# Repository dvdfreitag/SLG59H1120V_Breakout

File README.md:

# SLG59H1120V_Breakout
A SLG59H1120V breakout board

The [SLG59H1120V](https://www.digikey.com/product-detail/en/silego-technology/SLG59H1120V/1827-1055-1-ND/7562939) is an extremely inexpensive high side power switch with a rich feature set. This chip has built in current limiting with a current set resistor, soft start, thermal cutoff, configurable input over voltage protection, short circuit protection, current output, and an open drain fault interrupt.

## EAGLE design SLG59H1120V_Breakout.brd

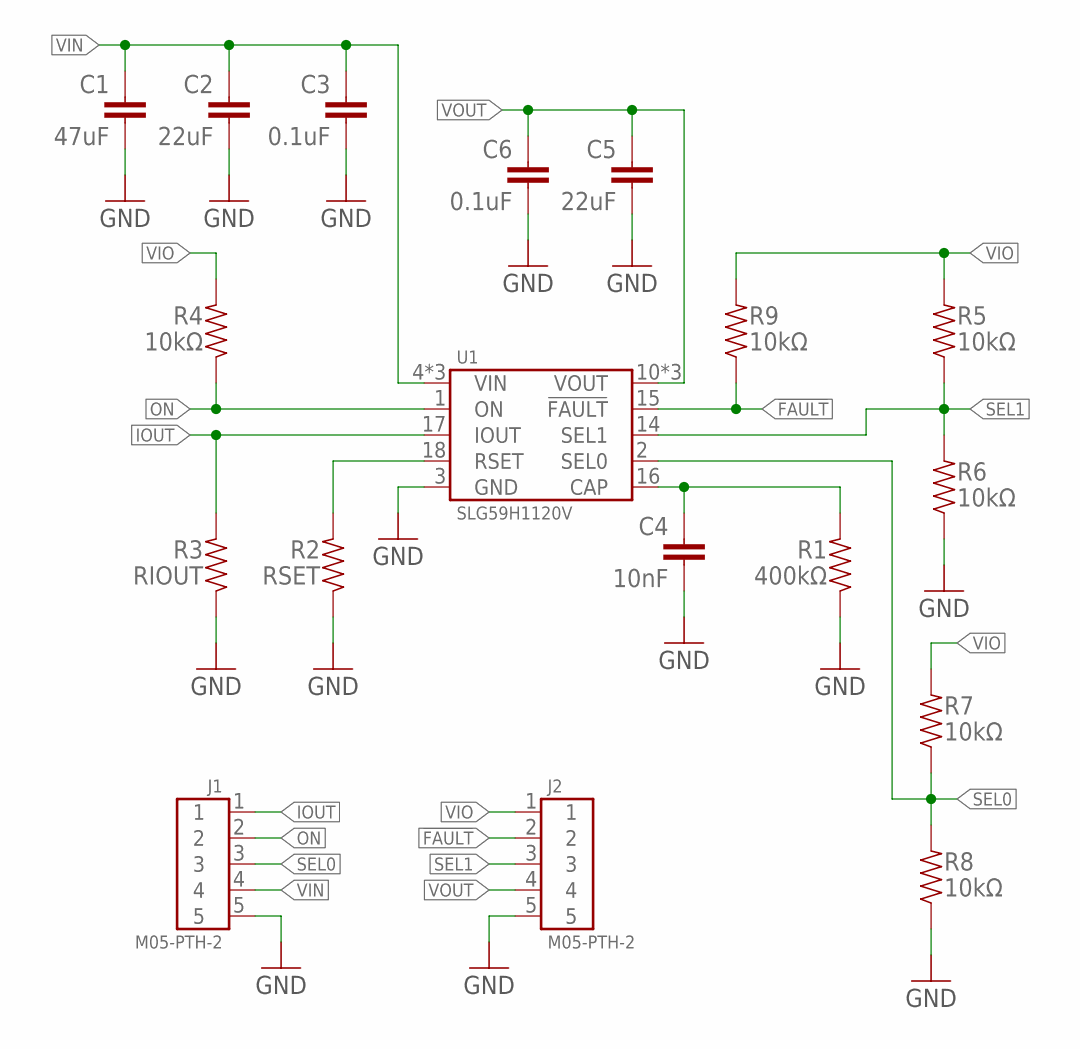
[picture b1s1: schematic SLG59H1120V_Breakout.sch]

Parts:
C1: 47uF; 1206
C2, C5: 22uF; 1206
C3, C6: 0.1uF; 0603-CAP
C4: 10nF; 0603-CAP
J1, J2: M05-PTH-2; M05-2
R1: 400kΩ; 0603-CAP
R2: RSET; 0603-CAP
R3: RIOUT; 0603-CAP
R4, R5, R6, R7, R8, R9: 10kΩ; 0603-CAP
U1: SLG59H1120V; STQFN-18-1.6X3

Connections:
!FAULT: J2.2, R9.1, U1.15 (!FAULT)
GND: C1.2, C2.2, C3.2, C4.2, C5.2, C6.2, J1.5, J2.5, R1.1, R2.1, R3.1, R6.1, R8.1, U1.3 (GND)
IOUT: J1.1, R3.2, U1.17 (IOUT)
unnamed: R2.2, U1.18 (RSET)
unnamed: C4.1, R1.2, U1.16 (CAP)
ON: J1.2, R4.1, U1.1 (ON)
SEL0: J1.3, R7.1, R8.2, U1.2 (SEL0)
SEL1: J2.3, R5.1, R6.2, U1.14 (SEL1)
VIN: C1.1, C2.1, C3.1, J1.4, U1.4 (VIN), U1.5 (VIN), U1.6 (VIN)
VIO: J2.1, R4.2, R5.2, R7.2, R9.2
VOUT: C5.1, C6.1, J2.4, U1.10 (VOUT), U1.11 (VOUT), U1.12 (VOUT)

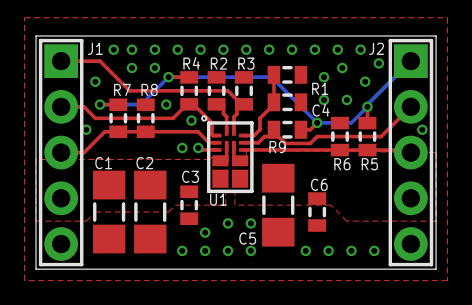
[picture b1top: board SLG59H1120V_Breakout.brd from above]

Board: 2 copper layers, 22.2 x 13.0 mm, 18 parts (0 on the bottom side), 11 nets.

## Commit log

2018-04-29 Create LICENSE
2018-04-29 Add schematic pdf
2018-04-29 Add paste gerber
